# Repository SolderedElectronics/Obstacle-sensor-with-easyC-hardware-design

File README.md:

# Obstacle sensor with easyC Hardware design

## About the product

|  |
| :----------------------------------------------------------: |
|      [Buy Obstacle sensor with easyC](https://www.solde.red/333004)      |

------ product description ------

## Repository contents

All Soldered Electronics hardware designed in KiCAD, and repositories are organized in the following way:

- CAD folder - contains KiCAD files (Schematics, Board, Panel Board), sorted by version. Change log lists all changes between versions.
- OUTPUTS - contains useful files, such as Bill of Materials (BOM), PDF of schematics, 3D .step file of the board and gerber files, sorted by version. 
- OUTPUTS -> Compliance - Certificates and useful legal stuff. 

## Want to contribute?

Please feel free to submit a pull request if you have any contributions. We encourage you to submit an issue or pull request if you find a bug. 

## About Soldered

At Soldered, we design and manufacture a wide selection of electronic products to help you turn your ideas into acts and bring you one step closer to your final project. Our products are intented for makers and crafted in-house by our experienced team in Osijek, Croatia. We believe that sharing is a crucial element for improvement and innovation, and we work hard to stay connected with all our makers regardless of their skill or experience level. Therefore, all our products are open-source. Finally, we always have your back. If you face any problem concerning either your shopping experience or your electronics project, our team will help you deal with it, offering efficient customer service and cost-free technical support anytime. Some of those might be useful for you:

- [Web Store](https://www.soldered.com/shop)
- [Tutorials & Projects](https://soldered.com/learn)
- [Community & Technical support](https://soldered.com/community)

## License info

All Soldered open-source hardware (OSH) is under The TAPR Open Hardware License. Read more in the LICENSE file. 

No warranty - all designs in this repository are distributed in the hope that they will be useful, but without any warranty. They are provided "AS IS", therefore without warranty of any kind, either expressed or implied. The entire quality and performance of what you do with the contents of this repository are your responsibility. In no event, Soldered Electronics will be liable for your damages, losses, including any general, special, incidental or consequential damage arising out of the use or inability to use the contents of this repository. 

## Have fun! 
And thank you from your fellow makers at Soldered Electronics.

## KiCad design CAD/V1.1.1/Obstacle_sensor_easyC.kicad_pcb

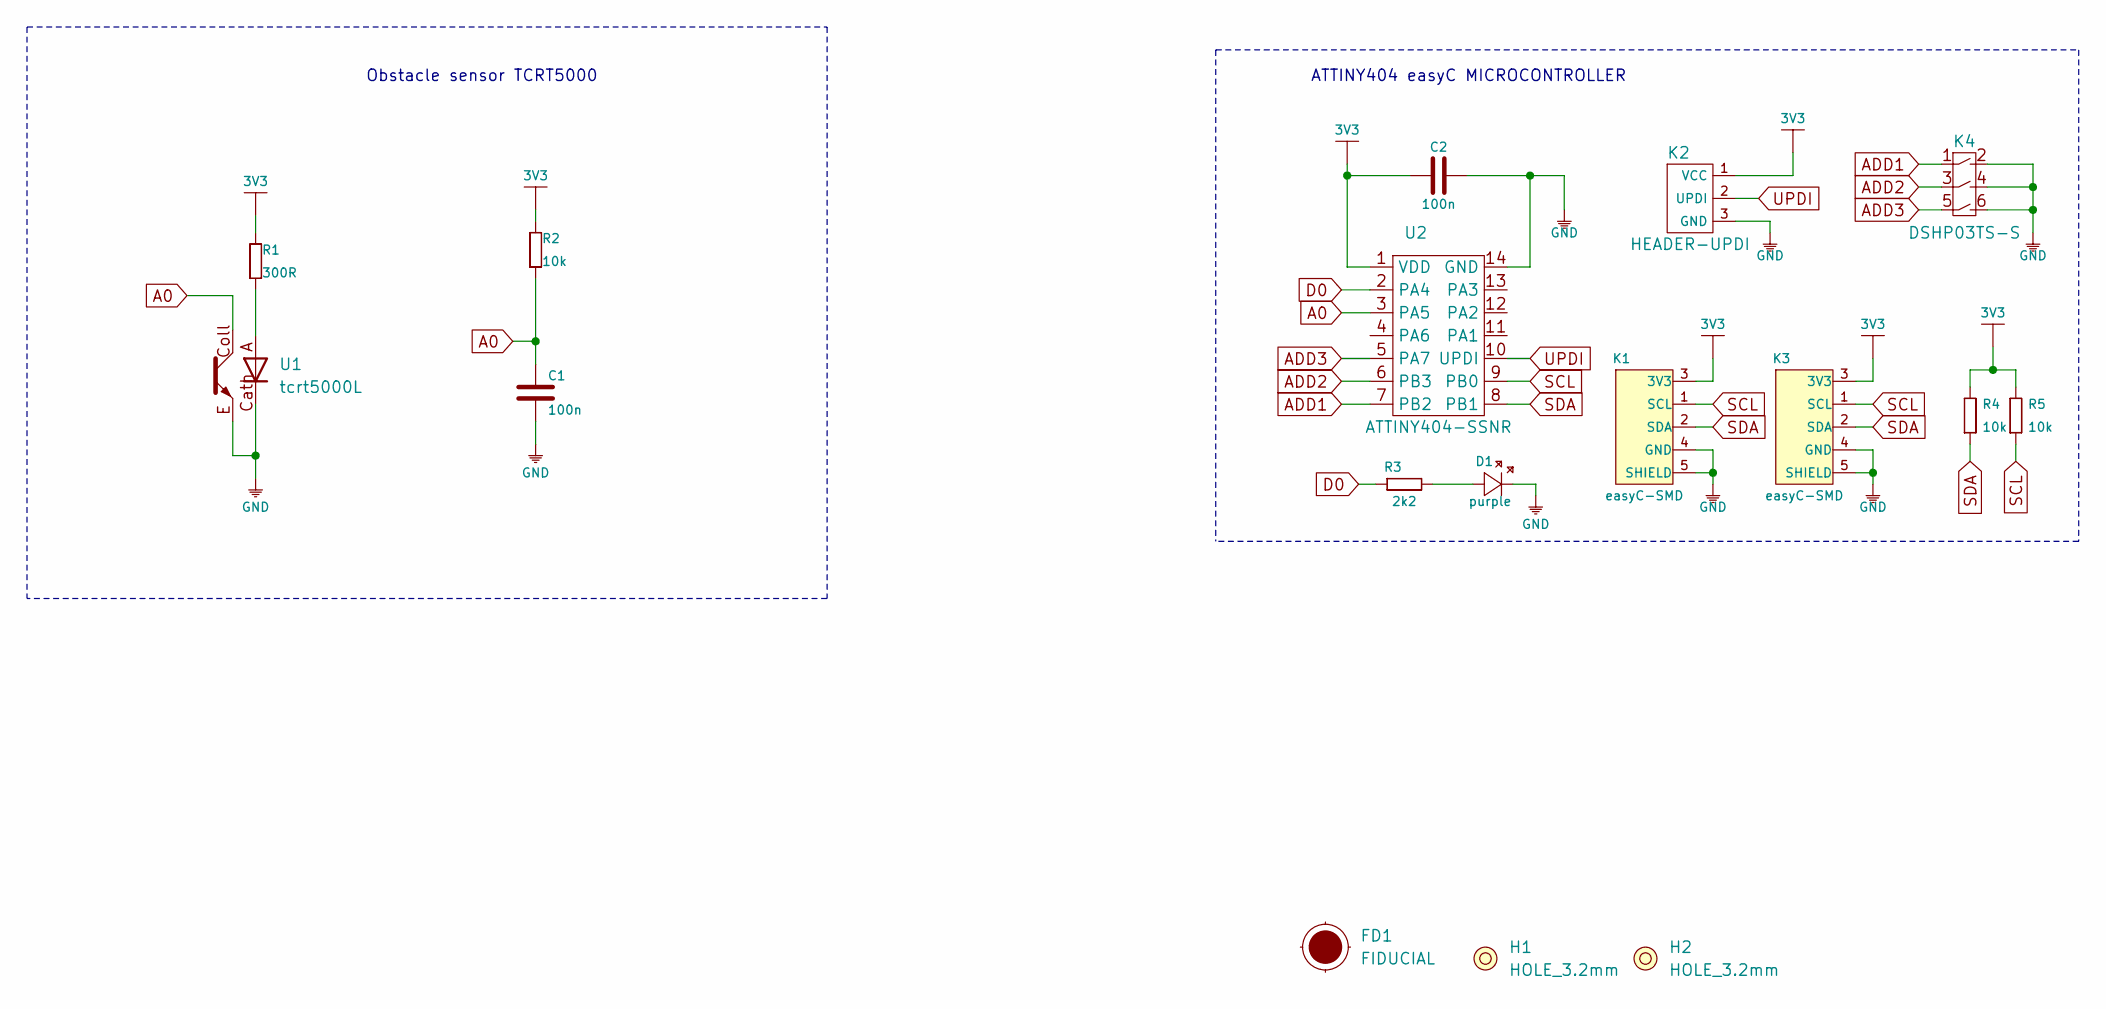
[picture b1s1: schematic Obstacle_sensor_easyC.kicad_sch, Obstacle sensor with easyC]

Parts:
C1, C2: 100n; 0603C
D1: purple; 0402LED
FD1: FIDUCIAL; FIDUCIAL_23
H1, H2: HOLE_3.2mm
K1, K3: easyC-SMD; easyC-connector
K2: HEADER-UPDI
K4: DSHP03TS-S
R1: 300R; 0603R
R2, R4, R5: 10k; 0603R
R3: 2k2; 0402R
U1: tcrt5000L; TCRT5000L
U2: ATTINY404-SSNR; SOIC-14

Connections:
3V3: C2.1, K1.3 (3V3), K2.1 (VCC), K3.3 (3V3), R1.2, R2.2, R4.2, R5.2, U2.1 (VDD)
A0: C1.2, R2.1, U1.Coll, U2.3 (PA5)
ADD1: K4.1, U2.7 (PB2)
ADD2: K4.3, U2.6 (PB3)
ADD3: K4.5, U2.5 (PA7)
D0: R3.1, U2.2 (PA4)
GND: C1.1, C2.2, D1.2 (K), K1.4 (GND), K1.5 (SHIELD), K2.3 (GND), K3.4 (GND), K3.5 (SHIELD), K4.2, K4.4, K4.6, U1.Cath, U1.E, U2.14 (GND)
unnamed: D1.1 (A), R3.2
unnamed: R1.1, U1.A
SCL: K1.1 (SCL), K3.1 (SCL), R5.1, U2.9 (PB0)
SDA: K1.2 (SDA), K3.2 (SDA), R4.1, U2.8 (PB1)
UPDI: K2.2 (UPDI), U2.10 (UPDI)

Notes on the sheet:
Obstacle sensor TCRT5000
ATTINY404 easyC MICROCONTROLLER

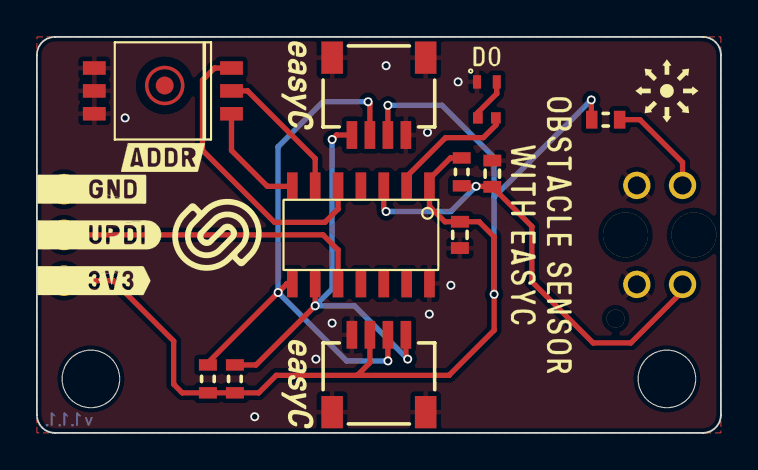
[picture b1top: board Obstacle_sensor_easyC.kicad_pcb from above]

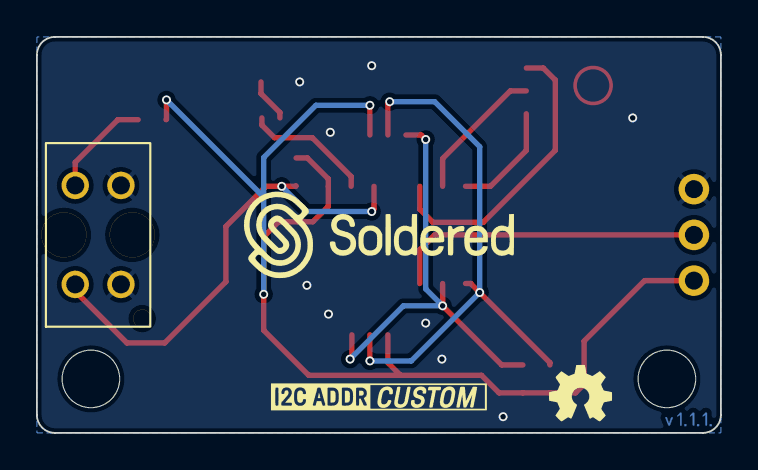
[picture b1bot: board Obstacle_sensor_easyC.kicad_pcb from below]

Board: 2 copper layers, 38.0 x 22.0 mm, 17 parts (2 on the bottom side), 12 nets.

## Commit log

2022-08-06 Updating open source files.
